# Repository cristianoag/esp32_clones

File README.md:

# The Retro Hacker Clone Series

The Retro Hacker Clone Series brings together hardware designs and source-available firmware to recreate and emulate classic computers from the 1980s and 1990s using modern ESP32 based hardware.

 The board is designed to feel like a small retro computer rather than a bare dev board, and the firmwares are built to be practical, tweakable, and easy to build from a standard Git checkout.

## Hardware versions

The series now has two hardware versions that share the same outline, mounting holes and connector layout:

| Version | Module | Audio | KiCad project |
| --- | --- | --- | --- |
| ESP32-S3 | ESP32-S3 dev board (N16R8) | Mono | [hardware/esp32_s3_clones](hardware/esp32_s3_clones) |
| ESP32-P4 | Waveshare ESP32-P4-Core-DEV-KIT | Stereo | [hardware/esp32_p4_clones](hardware/esp32_p4_clones/README.md) |

## Software

At the moment the series includes eight emulator builds, all for the ESP32-S3 board. There is no firmware for the ESP32-P4 board yet.

| Firmware | Covered machines | ESP32-S3 | ESP32-P4 |
| --- | --- | --- | --- |
| CP400 | Prologica CP400 / CoCo 2 | [Setup guide](software/esp32_s3_cp400/README.md) and [change log](software/esp32_s3_cp400/docs/log.md) | Not available yet |
| MSX | MSX1, MSX2, and MSX2+ | [Setup guide](software/esp32_s3_msx/README.md) and [change log](software/esp32_s3_msx/docs/log.md) | Not available yet |
| MSX TurboR (experimental) | Panasonic FS-A1ST | [Setup guide](software/esp32_s3_msxturbor/README.md), [license report](software/esp32_s3_msxturbor/docs/licenses.md) and [change log](software/esp32_s3_msxturbor/docs/log.md) | Not available yet |
| TK90X / TK95 | Microdigital TK90X (48 KiB) and TK95 | [Setup guide](software/esp32_s3_tk95/README.md) and [change log](software/esp32_s3_tk95/docs/log.md) | Not available yet |
| Apple II | Generic Apple II+ and original Apple IIe | [Setup guide](software/esp32_s3_apple2/README.md) and [change log](software/esp32_s3_apple2/docs/log.md) | Not available yet |
| Macintosh Plus | Apple Macintosh Plus | [Setup guide](software/esp32_s3_macplus/README.md) and [change log](software/esp32_s3_macplus/docs/log.md) | Not available yet |
| Sega Master System | Sega Master System (NTSC / PAL) | [Setup guide](software/esp32_s3_sms/README.md) and [change log](software/esp32_s3_sms/docs/log.md) | Not available yet |
| Commodore 64 | Commodore 64 (PAL) | [Setup guide](software/esp32_s3_c64/README.md), [licenses](software/esp32_s3_c64/docs/licenses.md) and [change log](software/esp32_s3_c64/docs/log.md) | Not available yet |

> **Development status:** all firmwares are under active development and at different maturity stages. The CP400 and MSX firmwares are the most mature; the others (including the experimental MSX TurboR) are earlier-stage and may be incomplete or change significantly.

All eight builds share the same ESP32-S3 board, VGA output, USB keyboard input, SD-card storage, and a simple F12 menu for setup and firmware updates.

## User guides

- [Quick Start](docs/quick-start.md): connect the monitor, keyboard and
  joysticks, turn on/reset the computer, and switch firmware through F12.
- [User Manual](docs/user-manual.md): SD-card preparation, controller
  compatibility, game-loading steps for all eight firmwares, and troubleshooting.

### Switching emulators

With the current updater and shared dual 4 MiB OTA layout installed, open
**F12 > Firmware update** in any emulator and select another emulator's
`.FLH` package. For example, MSX can install CP400, and CP400 can then
install Apple II. No renaming is needed. Copy the packages to the FAT32
card root (required by CP400's file picker), prepare the destination
emulator's ROMs using its setup guide, confirm the update and keep power
connected until the board restarts. The original FLH stays on the card.

Build packages with `make firmware` in each firmware folder. Older MSX,
TK and Apple updaters reject other emulator filenames: first update to
the current build of the **same** emulator. Older CP400 installations use
a smaller partition layout and require a **one-time UART upload** of a
current build before switching via SD. FLH updates replace only the
application, not the bootloader or partition table. Use current builds
for every destination so switching remains available after reboot.
Checksums detect corruption, not authenticity; install only trusted
firmware built for this board.

After building all eight packages, run
`powershell -ExecutionPolicy Bypass -File .\software\Test-FirmwareCompatibility.ps1`
to check the shared layout and all 64 source/destination combinations
against mock OTA storage. Physical-board switching still needs validation.

## Commodore 64

The [C64 firmware](software/esp32_s3_c64/README.md) adapts the
CPU, CIA, VIC-II and SID from
[retroelec/T-HMI-C64](https://github.com/retroelec/T-HMI-C64) to the shared
VGA board. It includes a USB C64 keyboard matrix, two calibrated USB
joysticks with port swapping, PWM sound, PRG loading, read-only D64 program
extraction, the F12 configuration menu and interchangeable FLH firmware.
Supply your own BASIC, KERNAL and character ROMs. The initial version
does not emulate a 1541 drive, cartridges or tapes, and does not claim
cycle accuracy or verified physical-board performance.

## CP400

The Prologica CP400 was one of the more recognizable Brazilian home computers of the 1980s. It was compatible with the Tandy/Radio Shack TRS-80 Color Computer 2, but it had its own industrial design, Brazilian-language software ecosystem, and local hardware expectations.

The [CP400 firmware](software/esp32_s3_cp400/README.md) recreates that environment on ESP32-S3 hardware, including MC6809 emulation, VGA output, native USB keyboard support, joystick inputs, SD storage, virtual floppy handling, and the F12 configuration/update menu.

## MSX

The MSX has a very special place in Brazilian computing history. It officially arrived in Brazil in 1985 through two locally produced machines: the HotBit, from Sharp/Epcom, and the Expert, from Gradiente. At a time when Brazil’s computer market was heavily restricted and imported machines were difficult and expensive to obtain, the MSX became one of the country’s most important home-computing platforms. Its standardized architecture, large software library, expandability, and built-in BASIC introduced an entire generation not only to games, but also to programming, electronics, and computer technology. 

The [MSX firmware](software/esp32_s3_msx/README.md) runs the original fMSX core on the same shared board. It includes multiple BIOS profiles for Omega MSX2+, Gradiente Expert 1.1, Sharp Hotbit 1.2, and Panasonic FS-A1WSX / FS-A1F / FS-A1FX.

The software supports the core MSX experience with USB keyboard input, graphics, sound, cartridge booting, and firmware updates through the on-screen menu. and... USB joystick support, of course.

The F12 Media menu attaches writable `.dsk` images to drives A/B and read-only `.cas` tapes, with ejection, tape rewind and optional saved boot defaults. Disk access requires a compatible user-supplied disk BIOS; see the [disk and tape setup guide](software/esp32_s3_msx/README.md#disk-and-tape-images).

## MSX TurboR / Panasonic FS-A1ST

The experimental [MSX TurboR firmware](software/esp32_s3_msxturbor/README.md)
recreates the Panasonic FS-A1ST using a source subset of blueMSX, separate
from the ordinary fMSX-based MSX build. It includes Z80/R800 switching,
DRAM mode, V9958 graphics, PSG, MSX-MUSIC, PCM output and writable
360/720 KiB `.dsk` images through the original disk interface.

Supply your own FS-A1ST firmware and Kanji ROMs under
`msxturbor/bios/fs-a1st` on the FAT32 card. See the
[SD card and ROM setup](software/esp32_s3_msxturbor/README.md#prepare-the-sd-card),
[scope and limitations](software/esp32_s3_msxturbor/README.md#implementation-scope-and-limitations)
and [licenses and provenance](software/esp32_s3_msxturbor/docs/licenses.md).
The original BIOS boots into MSX BASIC in host tests; physical-board
performance, VGA/audio quality and firmware switching still require
validation. A1GT/MIDI and full-speed emulation are not claimed.

## TK90X / TK95

The Microdigital TK90X and TK95 brought the ZX Spectrum family of computers to Brazilian homes. The [TK firmware](software/esp32_s3_tk95/README.md) emulates the TK95 and 48 KiB TK90X on the same shared ESP32-S3 board, using
the cycle-stepped chips Z80 core.

The firmware includes VGA output, USB keyboard input, beeper audio and two USB joystick ports with calibration and selectable Kempston, Sinclair 1/2 or Cursor interfaces. The F12 menu brings together machine and ROM selection, 50/60 Hz Microdigital ULA timing, Portuguese/Spanish ROM language selection, sound and volume, saved boot defaults, reset options and firmware updates.

Media support includes read-only standard `.tap` playback and loading 48K `.sna` and `.z80` snapshots. Supply legally obtained, raw 16 KiB ROMs at `tk\bios\tk95.rom` and `tk\bios\tk90.rom` on the FAT32 card; the `tk` folder can sit alongside `msx` and `cp400`. No ROM bytes are embedded in the firmware.

See the [SD card and ROM setup](software/esp32_s3_tk95/README.md#sd-card-and-roms) and [keyboard guide](software/esp32_s3_tk95/README.md#keyboard-and-joysticks) for the original TK keyword-entry conventions.

The initial release does not include AY audio, Betadisk, TZX, tape recording or snapshot saving, and does not claim full cycle accuracy. 

## Apple II

The [Apple II firmware](software/esp32_s3_apple2/README.md) adds generic
Apple II+ (64 KiB with language card) and original Apple IIe (128 KiB)
profiles. It follows the shared standalone PlatformIO, board-driver, F12
configuration and FLH firmware-update conventions.

The initial integration uses
[codesafe/ESP32-VGA_AppleII_Emulator](https://github.com/codesafe/ESP32-VGA_AppleII_Emulator)
as its starting reference, with a cycle-stepped NMOS 6502 and additional
IIe banking and display support. VGA preserves the full width of
80-column text; USB keyboard, calibrated joystick/paddle input, speaker
audio and two read-only NIB Disk II drives are included.

Supply machine and Disk II ROMs under `apple2/bios` on SD. No ROMs or games
are distributed. Enhanced IIe/65C02 and Brazilian TK2000, TK3000/Compact,
MC-4000/Exato and Exato IIe profiles are not claimed as supported without
their required hardware and verified ROMs. See the
[scope and limitations](software/esp32_s3_apple2/README.md#supported-media-and-limitations).
Physical-board validation is still pending.

## Macintosh Plus

The [Macintosh Plus firmware](software/esp32_s3_macplus/README.md)
integrates a Musashi 68000 and Macintosh peripheral core with 4 MiB of
emulated RAM, a native 512x342 monochrome image centered on 640x480 VGA,
USB keyboard input, mono audio and the shared F12 menu and FLH updater.
A direct low-speed HID boot mouse connects to **joystick port 2**;
full-speed-only mice and USB hubs are unsupported.

Supply an unmodified 128 KiB Macintosh Plus ROM and a bootable whole
SCSI disk image under `macplus/bios` and `macplus/disks` on the FAT32 card.
No Apple ROM, operating system or disk image is bundled. See the
[SD card, ROM and disk setup](software/esp32_s3_macplus/README.md#sd-card-and-rom),
[mouse compatibility](software/esp32_s3_macplus/README.md#mouse-compatibility)
and [scope and validation](software/esp32_s3_macplus/README.md#scope-and-validation).
This is an initial integration, not a claim of full-speed or cycle-accurate
emulation; floppy-media support is not implemented.

## Repository layout

```text
hardware/esp32_s3_clones/          KiCad PCB and shared board files
hardware/esp32_s3_clones/libraries Local KiCad symbols and footprints
hardware/esp32_s3_clones/bom       Interactive BOM and BOM assets
hardware/esp32_p4_clones/          KiCad PCB for the ESP32-P4 (stereo audio) variant, see its README
hardware/cases/standard/       Parametric printed base, acrylic lid and manufacturing exports
software/esp32_s3_cp400/  PlatformIO firmware for the CP400 build
software/esp32_s3_msx/    MSX firmware and setup files
software/esp32_s3_msxturbor/ MSX TurboR / Panasonic FS-A1ST firmware and setup files
software/esp32_s3_tk95/   TK90X/TK95 firmware and setup files
software/esp32_s3_apple2/ Apple II+/original IIe firmware and setup files
software/esp32_s3_macplus/ Macintosh Plus firmware and setup files
images/                         Generated images and project documentation assets
```

## Board renderings

For the first enclosure prototype, see the
[standard case manufacturing files and engineering report](hardware/cases/standard/README.md).
P4 combines a printed base with easy-loading PCB nut traps, a screw-fastened
upper and a drilled 3 mm acrylic lid. Four M3 x 25 nylon screws pass down through
the acrylic into base nuts. Its vented alternative uses a separate matching
base with recessed bottom-entry screws and upper nuts. The acrylic cutting
pattern is [lid.dxf](hardware/cases/standard/lid.dxf); do not reuse the old
plain panel. See the report for dimensions and remaining physical-fit checks.

The Hotbit-inspired **Compact Classic C6** fits the same PCB in a
**124 x 74 x 39.1 mm** case, reducing the earlier Classic footprint by 26.9%.
It retains the miniature keyboard, photo-inspired colours and closed decorative
grille, with underside M3 cover screws. Use the matching
[base STL](hardware/cases/hb-8000/classic_base.stl) and
[upper STL](hardware/cases/hb-8000/classic_upper.stl); do not mix these with older
Classic or Wasteland halves. See the
[assembled/exploded preview](hardware/cases/hb-8000/classic_preview.png).
Print both STLs at 100%; the upper needs removable interior supports.
PCB screws remain M3 x 8 with 1 mm nylon washers; cover screws are M3 x 25 nylon,
with four M3 hex nuts for each set. Physical plug-fit and thermal tests are
still required; the decorative grille is not a ventilation opening.

The [Sony S2](hardware/cases/sony/README.md),
[Panasonic P2](hardware/cases/panasonic/README.md) and
[Apple II A3](hardware/cases/apple2/README.md) now share the C6 base and its
bottom-entry shell fastening. Their matching uppers replace the old clip joints.

The [Mac Plus-inspired M1](hardware/cases/mac/README.md) uses the same C6 base
under a **124 x 74 x 146.1 mm upright tower**, with a separate dark decorative
screen and miniature keyboard. Its blind floppy-slot detail, top grilles and
handle-shaped recess follow the supplied visual reference; no working display,
keyboard electronics or load-bearing handle is included. See the
[assembly and print-layout preview](hardware/cases/mac/mac_preview.png).

The [CP400-inspired CP1](hardware/cases/cp400/README.md) also reuses the C6
base in the compact **124 x 74 x 39.1 mm** envelope. Its left keyboard, raised
right panel and horizontal rear grilles follow the supplied photograph.
Integral and separate-keyboard upper options are available; red/green/cyan
accents in the [preview](hardware/cases/cp400/cp400_preview.png) are a painting
guide, not separate key pieces.

The [Master System-inspired SMS1](hardware/cases/sms/README.md) uses the same
C6 base and **124 x 74 x 39.1 mm** envelope, with an angular black console
shell and one separately printed red top-panel/front-stripe insert.
Cartridge/card slots and control shapes are decorative; no joystick or
controller is modelled. See the
[assembly and print-layout preview](hardware/cases/sms/sms_preview.png).

The PCB below is the current KiCad board layout for the shared ESP32 clone board. The front and back views are generated directly from the project PCB.

<div align="center">

</div>

For the full component-by-component assembly view, open the [interactive BOM](https://htmlpreview.github.io/?https://raw.githubusercontent.com/cristianoag/esp32_clones/blob/main/hardware/esp32_s3_clones/bom/ibom.html).

## Hardware summary

The ESP32-S3 board is built around an ESP32-S3 DevKitC-style N16R8 module with 16 MB flash and 8 MB OPI PSRAM. It includes VGA output, a USB keyboard port, SD/MMC storage, a mono audio output, and a compact layout intended to behave more like a small computer than a bare dev board.

The ESP32-P4 board keeps the same outline, VGA output, USB-A ports, SD card slot and connector positions, but uses the Waveshare ESP32-P4-Core-DEV-KIT (32 MB flash, 32 MB PSRAM) and adds a stereo audio output.

The ESP32-S3 board is used by all eight firmware projects, and the pin mapping is documented in the [MSX hardware section](software/esp32_s3_msx/README.md#hardware), the [MSX TurboR hardware section](software/esp32_s3_msxturbor/README.md#hardware-and-dependencies), the [TK hardware section](software/esp32_s3_tk95/README.md#hardware), the [Apple II hardware section](software/esp32_s3_apple2/README.md#hardware) and the [Macintosh Plus hardware section](software/esp32_s3_macplus/README.md#hardware).

## BOM and purchasing

This is the current BOM for the board as defined in the KiCad project. The table is meant to be a quick parts reference for ordering and build prep.

| Component | Description | Qty | Package | AliExpress |
| --- | --- | ---: | --- | --- |
| C1 | 220 µF electrolytic capacitor | 1 | 6.3x3 mm | [AliExpress](https://s.click.aliexpress.com/e/_c3vZZzuN) |
| C2 | 10 µF electrolytic capacitor | 1 | 5x4.5 mm | [AliExpress](https://s.click.aliexpress.com/e/_c3vZZzuN) |
| C4 | 100 nF ceramic capacitor | 1 | 0805 | [AliExpress](https://s.click.aliexpress.com/e/_c31gzw17) |
| C6 | 47 nF ceramic capacitor | 1 | 0805 | [AliExpress](https://s.click.aliexpress.com/e/_c31gzw17) |
| F1 | Resettable fuse / polyfuse | 1 | 1210 | [AliExpress](https://s.click.aliexpress.com/e/_c36cHi81) |
| J1 | DC barrel jack | 1 | Horizontal | [AliExpress](https://s.click.aliexpress.com/e/_c3D102dx) |
| J2 | Micro SD card socket | 1 | uSD | [AliExpress](https://s.click.aliexpress.com/e/_c3odXI41) |
| J3 | 3.5 mm audio jack | 1 | PJ-307 | [AliExpress](https://s.click.aliexpress.com/e/_c4DX94lF) |
| J4 | 12V power header / connector | 1 | PS-12E05 | [AliExpress](https://s.click.aliexpress.com/e/_c42cnGRn) |
| J5 | 5V power header / connector | 1 | PS-22F05 | [AliExpress](https://s.click.aliexpress.com/e/_c35YnsCh) |
| J6–J8 | USB-A connector | 3 | TE 6364372-2 | [AliExpress](https://s.click.aliexpress.com/e/_c4afTAHb) |
| J9 | DB15 video connector | 1 | D-sub 15-pin | [AliExpress](https://s.click.aliexpress.com/e/_c3K7eRWv) |
| R1, R4, R7 | 10 kΩ resistor | 3 | 0805 | [AliExpress](https://s.click.aliexpress.com/e/_c2zrvGiH) |
| R8, R10, R12 | 1.2 kΩ resistor | 3 | 0805 | [AliExpress](https://s.click.aliexpress.com/e/_c2zrvGiH) |
| R9, R11, R13 | 560 Ω resistor | 3 | 0805 | [AliExpress](https://s.click.aliexpress.com/e/_c2zrvGiH) |
| R2, R5 | 330 Ω resistor | 2 | 0805 | [AliExpress](https://s.click.aliexpress.com/e/_c2zrvGiH) |
| U1 | ESP32-S3-WROOM-1 module | 1 | ESP32-S3-WROOM-1 | [AliExpress](https://s.click.aliexpress.com/e/_c2uppnEv) |

## Firmware build notes

Firmware project folders use `software/esp32_s3_<name>`, while update packages
retain their existing `ESP32_<NAME>-X.YY.FLH` names.

All six firmware projects use PlatformIO with the Arduino framework and a pinned `espressif32@6.11.0` platform. From the project directory you want to use, run:

```powershell
Set-Location .\software\esp32_s3_cp400
# or:
# Set-Location .\software\esp32_s3_msx
# or:
# Set-Location .\software\esp32_s3_msxturbor
# or:
# Set-Location .\software\esp32_s3_tk95
# or:
# Set-Location .\software\esp32_s3_apple2
# or:
# Set-Location .\software\esp32_s3_macplus

make firmware
```

The build produces FLH packages for each target; the project directories keep their own firmware images and configuration.
From `software`, run `make` to prepare the shared SD-card tree and copy each
emulator's highest-versioned `dist\ESP32_*-X.YY.FLH` package only to the root of
`software\sdcard`. Firmware packages are copied
after merging the SD-card trees, including with parallel `make`.
Run `make firmware` there to copy packages only, or `make sdcard`
to prepare the SD-card tree only. Packages are not rebuilt; if any emulator is
missing a package, copying fails before any firmware files are deleted or copied.
Before copying, all FLH files directly in the shared SD-card root are deleted,
leaving only the latest package for each emulator. Emulator project roots and
`dist` archives are left unchanged, as are non-FLH files and nested folders
during firmware copying.
Each firmware directory includes its own board definitions and required
library sources and can be copied and compiled independently of the others.
All six still require PlatformIO and the configured ESP32 toolchain.

## ROMs and original software

Original CP400, CoCo, MSX, MSX TurboR, TK90X/TK95, ZX Spectrum, Apple II, Macintosh Plus, BASIC, cartridge, cassette, floppy and hard-disk software may still be copyrighted. This repository is for original hardware, firmware, and project files. Use legally obtained ROMs and software images when needed.

The CP400 firmware loads its BIOS files from `software/esp32_s3_cp400/sdcard/cp400/bios`. Copy the `cp400` folder to the root of the microSD card so the firmware can read the BASIC, Extended BASIC, and CP400 or CoCo disk controller ROM selected in the F12 menu.

## Historical notes

The CP400 was part of the wider Brazilian TRS-Color ecosystem, the MSX line became one of the most important home computer families in Brazil, and Microdigital's TK90X and TK95 connected Brazilian users to the ZX Spectrum ecosystem. This project sits at the intersection of those histories: a practical board, six emulator builds, and a small bit of preservation work for machines that still matter to a lot of people.

## References

- [Prologica CP-400](https://en.wikipedia.org/wiki/Prol%C3%B3gica_CP-400)
- [CP400](https://pt.wikipedia.org/wiki/CP400)
- [TRS-80 Color Computer](https://en.wikipedia.org/wiki/TRS-80_Color_Computer)
- [MSX](https://en.wikipedia.org/wiki/MSX)
- [fMSX by Marat Fayzullin](https://fms.komkon.org/fMSX/)
- [TK90X](https://en.wikipedia.org/wiki/TK90X)
- [TK95](https://en.wikipedia.org/wiki/TK95)
- [ESPectrum reference emulator](https://github.com/EremusOne/ESPectrum)
- [chips Z80 core](https://github.com/floooh/chips)
- [Prologica](https://pt.wikipedia.org/wiki/Prol%C3%B3gica)
- [Datassette](https://datassette.org/)

## License

All hardware and firmware binaries in this repository are released under the Creative Commons Attribution-NonCommercial-ShareAlike 4.0 International license. Personal builds and community tinkering are encouraged, but commercial use or resale requires explicit authorization from the author.

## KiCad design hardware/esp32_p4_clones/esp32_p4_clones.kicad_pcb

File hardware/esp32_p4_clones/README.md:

# ESP32-P4 Clone Board

KiCad 10 project for the ESP32-P4 version of the shared clone board. It reuses the
outline, mounting holes and connector positions of
[`../esp32_s3_clones`](../esp32_s3_clones) (110 x 60 mm), but carries a Waveshare
[ESP32-P4-Core-DEV-KIT](https://docs.waveshare.com/ESP32-P4-Core-DEV-KIT) instead of the
ESP32-S3 dev board, and has **stereo** audio.

Open `esp32_p4_clones.kicad_pro`. The libraries are local to the project
(`libraries/`), so no global library setup is needed.

## What changed from the S3 board

| Area | S3 board | P4 board |
| --- | --- | --- |
| Module | ESP32-S3 dev board, 2 x 22 pins | ESP32-P4-Core-DEV-KIT, 2 x 20 pins (28.62 x 58 mm), USB-C end towards the board edge |
| Audio | Mono, one filtered output feeding tip and ring | Stereo: two identical RC chains (330 Ω / 47 nF, 330 Ω / 100 nF, 10 µF coupling) feeding tip (left) and ring (right) |
| USB-A J7 | GPIO software host | Native USB 2.0 high-speed host (`DM`/`DP`) |
| Power into the module | `5V` pin | `VSYS` pin (the dev kit's own USB-C ports can also power the board) |
| Reset button J5 | `RST` | `RUN` (chip enable) |
| SD card | `DAT3` unconnected | `DAT3` pulled up with R4 (CLK has no pull-up) |

New or renumbered parts: C3 (10 µF), C5 (100 nF), C7 (47 nF), R3 and R6 (330 Ω) for the
right audio channel. Everything else keeps its S3 reference designator and footprint.

## GPIO map

| Function | Dev kit pin | Net |
| --- | --- | --- |
| VGA red (1.2 kΩ / 560 Ω) | GPIO4 / GPIO5 | `VGA_R0` / `VGA_R1` |
| VGA green (1.2 kΩ / 560 Ω) | GPIO9 / GPIO10 | `VGA_G0` / `VGA_G1` |
| VGA blue (1.2 kΩ / 560 Ω) | GPIO11 / GPIO13 | `VGA_B0` / `VGA_B1` |
| VGA HSYNC / VSYNC | GPIO3 / GPIO2 | `VGA_HS` / `VGA_VS` |
| Audio left / right | GPIO48 / GPIO47 | `AUDIO_L` / `AUDIO_R` |
| SD card CLK / CMD / DAT0 | GPIO46 / GPIO33 / GPIO32 | `SD_CLK` / `SD_CMD` / `SD_D0` |
| USB-A J7 (native) D- / D+ | DM / DP | `USB_DM` / `USB_DP` |
| USB-A J6 D- / D+ | GPIO26 / GPIO27 | `J6_DM` / `J6_DP` |
| USB-A J8 D- / D+ | GPIO20 / GPIO21 | `J8_DM` / `J8_DP` |
| Reset button | RUN | `RESET` |

GPIO2 to GPIO13 and GPIO20 to GPIO48 used above are all on the dev kit's 2.54 mm headers.
GPIO6, GPIO12, GPIO22, GPIO23, GPIO53 and GPIO54 are left unconnected. GPIO7 and GPIO8 are
the dev kit's I2C pins with 2.2 kΩ pull-ups, so they are also left free. `VBUS` and `EN`
are not connected.

## Check before ordering boards

- **Header row spacing is assumed to be 25.4 mm.** Waveshare publishes the board size
  (28.62 x 58 mm), the 2.54 mm pitch and the first pin 4.87 mm from each end, but not the
  distance between the two rows. Measure your dev kit and adjust the footprint
  (`libraries/footprints/ESP32.pretty/ESP32-P4-Core-DEV-KIT.kicad_mod`) if it differs.
- The dev kit's USB-C overhang and the 3D model (`libraries/ESP32-P4-Core-DEV-KIT.py`
  generates the STEP) are approximations.
- The PJ-307 jack pads are named `G`, `S` and `T`. They are wired as sleeve = `G`,
  tip (left) = `T`, ring (right) = `S`. If the channels come out swapped on your jack, swap
  `JACK_L` and `JACK_R`.
- The board was auto-routed with Freerouting and passes ERC and DRC. Review the routing,
  especially the J7 USB D+/D- pair, which is not length matched or impedance controlled.
- Do not feed 5 V into both the barrel jack and the dev kit's USB-C ports at the same time
  unless you are sure the supplies are compatible.

The remaining DRC warnings are silkscreen clearances on the connector footprints inherited
from the S3 board.

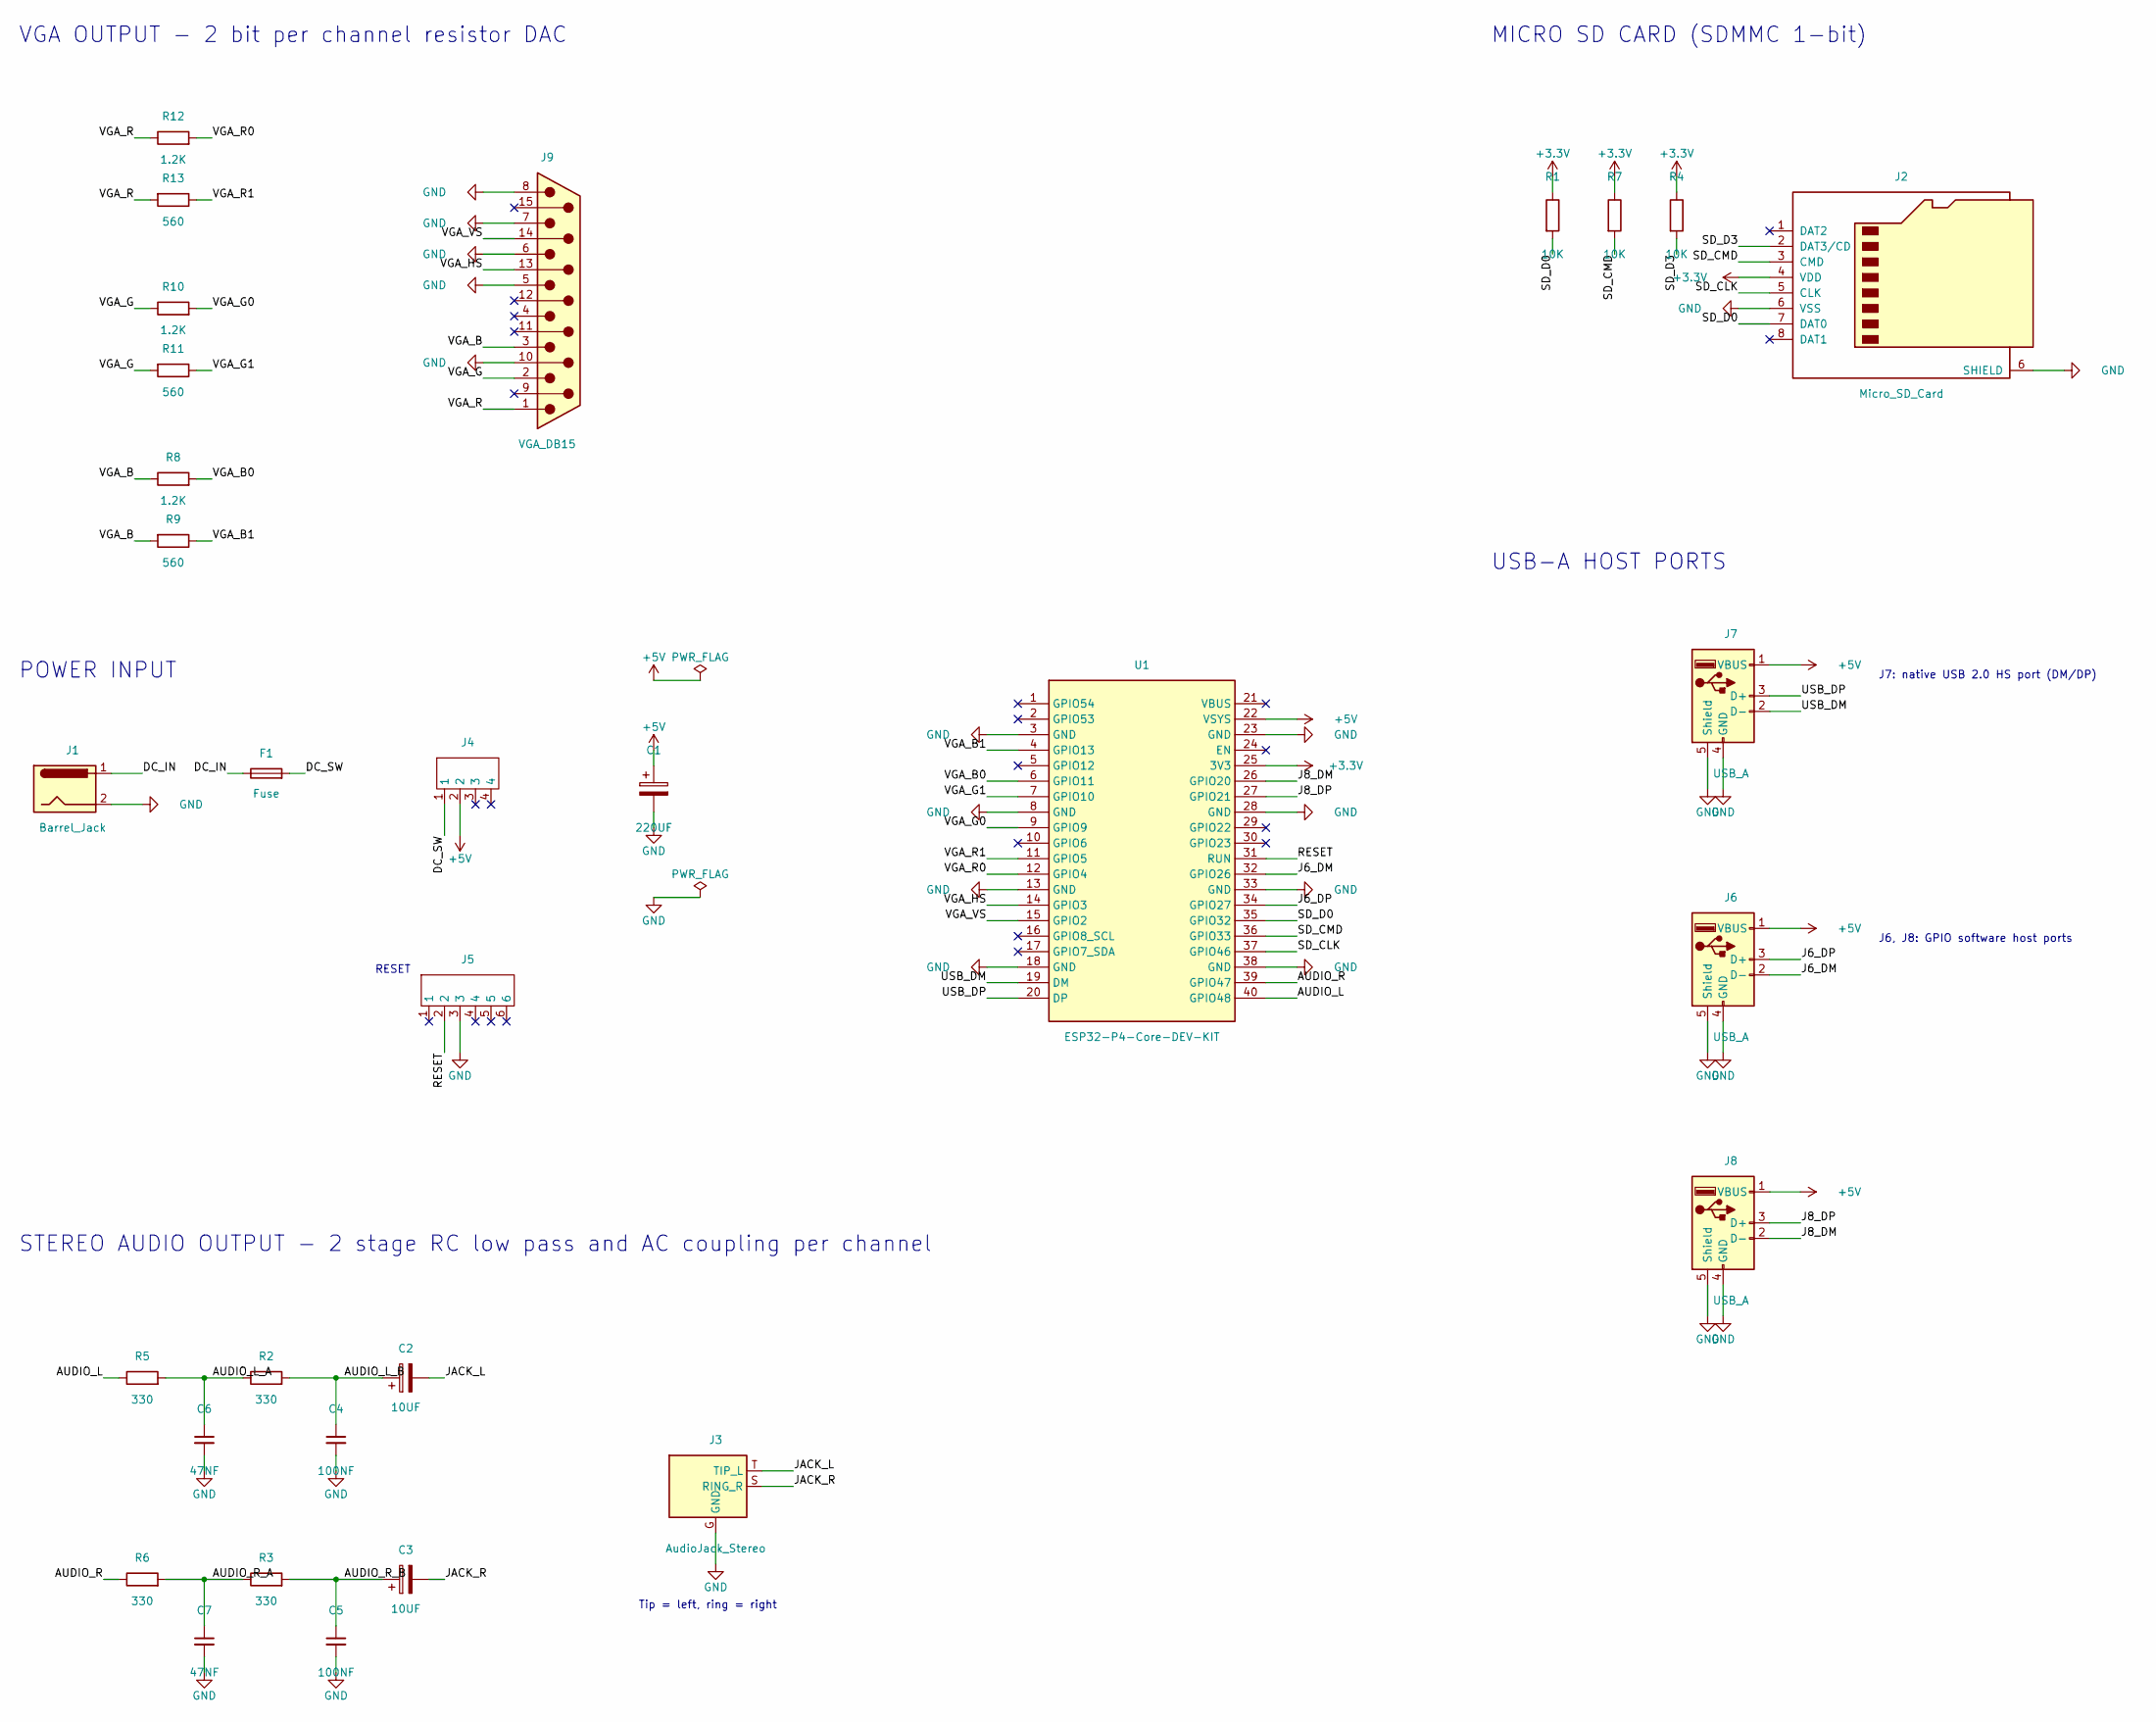
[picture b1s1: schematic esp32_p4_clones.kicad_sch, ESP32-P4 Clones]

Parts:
C1: 220UF; CP_Elec_6.3x3
C2, C3: 10UF; CP_Elec_5x4.5
C4, C5: 100NF; C_0805_2012Metric_Pad1.18x1.45mm_HandSolder
C6, C7: 47NF; C_0805_2012Metric_Pad1.18x1.45mm_HandSolder
F1: Fuse; Fuse_1210_3225Metric
J1: Barrel_Jack; BarrelJack_Horizontal
J2: Micro_SD_Card; Conn_uSDcard
J3: AudioJack_Stereo; PJ-307
J4: PS-12E05
J5: PS-22F05
J6, J7, J8: USB_A; TE_6364372-2
J9: VGA_DB15; DSUB-15-HD_Socket_Horizontal_P2.29x1.90mm_EdgePinOffset3.03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
R1, R4, R7: 10K; R_0805_2012Metric_Pad1.20x1.40mm_HandSolder
R2, R3, R5, R6: 330; R_0805_2012Metric_Pad1.20x1.40mm_HandSolder
R8, R10, R12: 1.2K; R_0805_2012Metric_Pad1.20x1.40mm_HandSolder
R9, R11, R13: 560; R_0805_2012Metric_Pad1.20x1.40mm_HandSolder
U1: ESP32-P4-Core-DEV-KIT

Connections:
+3.3V: J2.4 (VDD), R1.1, R4.1, R7.1, U1.25 (3V3)
+5V: C1.1, J4.2, J6.1 (VBUS), J7.1 (VBUS), J8.1 (VBUS), U1.22 (VSYS)
/AUDIO_L: R5.1, U1.40 (GPIO48)
/AUDIO_L_A: C6.1, R2.1, R5.2
/AUDIO_L_B: C2.1, C4.1, R2.2
/AUDIO_R: R6.1, U1.39 (GPIO47)
/AUDIO_R_A: C7.1, R3.1, R6.2
/AUDIO_R_B: C3.1, C5.1, R3.2
/DC_IN: F1.1, J1.1
/DC_SW: F1.2, J4.1
/J6_DM: J6.2 (D-), U1.32 (GPIO26)
/J6_DP: J6.3 (D+), U1.34 (GPIO27)
/J8_DM: J8.2 (D-), U1.26 (GPIO20)
/J8_DP: J8.3 (D+), U1.27 (GPIO21)
/JACK_L: C2.2, J3.T (TIP_L)
/JACK_R: C3.2, J3.S (RING_R)
/RESET: J5.2, U1.31 (RUN)
/SD_CLK: J2.5 (CLK), U1.37 (GPIO46)
/SD_CMD: J2.3 (CMD), R7.2, U1.36 (GPIO33)
/SD_D0: J2.7 (DAT0), R1.2, U1.35 (GPIO32)
/SD_D3: J2.2 (DAT3/CD), R4.2
/USB_DM: J7.2 (D-), U1.19 (DM)
/USB_DP: J7.3 (D+), U1.20 (DP)
/VGA_B: J9.3, R8.1, R9.2
/VGA_B0: R8.2, U1.6 (GPIO11)
/VGA_B1: R9.1, U1.4 (GPIO13)
/VGA_G: J9.2, R10.1, R11.2
/VGA_G0: R10.2, U1.9 (GPIO9)
/VGA_G1: R11.1, U1.7 (GPIO10)
/VGA_HS: J9.13, U1.14 (GPIO3)
/VGA_R: J9.1, R12.1, R13.2
/VGA_R0: R12.2, U1.12 (GPIO4)
/VGA_R1: R13.1, U1.11 (GPIO5)
/VGA_VS: J9.14, U1.15 (GPIO2)
GND: C1.2, C4.2, C5.2, C6.2, C7.2, J1.2, J2.6 (VSS), J3.G (GND), J5.3, J6.4 (GND), J6.5 (Shield), J7.4 (GND), J7.5 (Shield), J8.4 (GND), J8.5 (Shield), J9.5, J9.6, J9.7, J9.8, J9.10, U1.3 (GND), U1.8 (GND), U1.13 (GND), U1.18 (GND), U1.23 (GND), U1.28 (GND), U1.33 (GND), U1.38 (GND)

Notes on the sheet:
VGA OUTPUT - 2 bit per channel resistor DAC
POWER INPUT
RESET
MICRO SD CARD (SDMMC 1-bit)
USB-A HOST PORTS
J7: native USB 2.0 HS port (DM/DP)
J6, J8: GPIO software host ports
STEREO AUDIO OUTPUT - 2 stage RC low pass and AC coupling per channel
Tip = left, ring = right

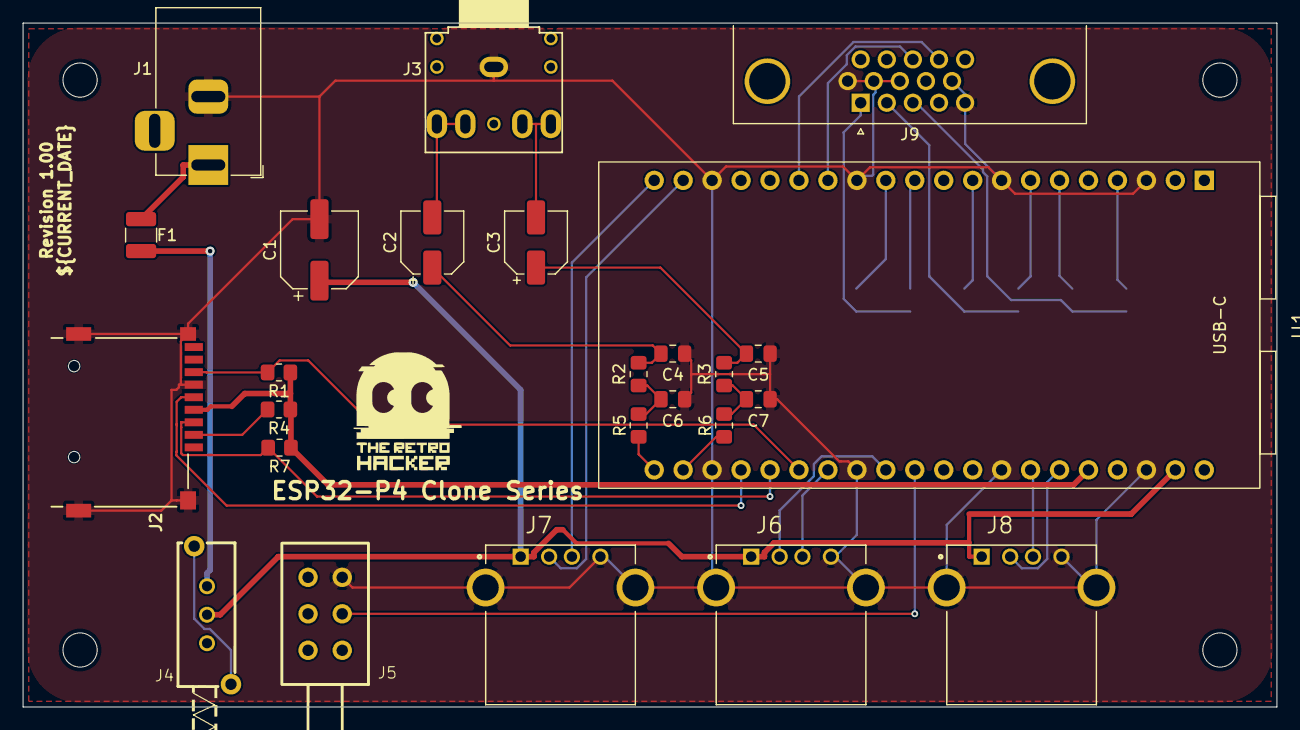
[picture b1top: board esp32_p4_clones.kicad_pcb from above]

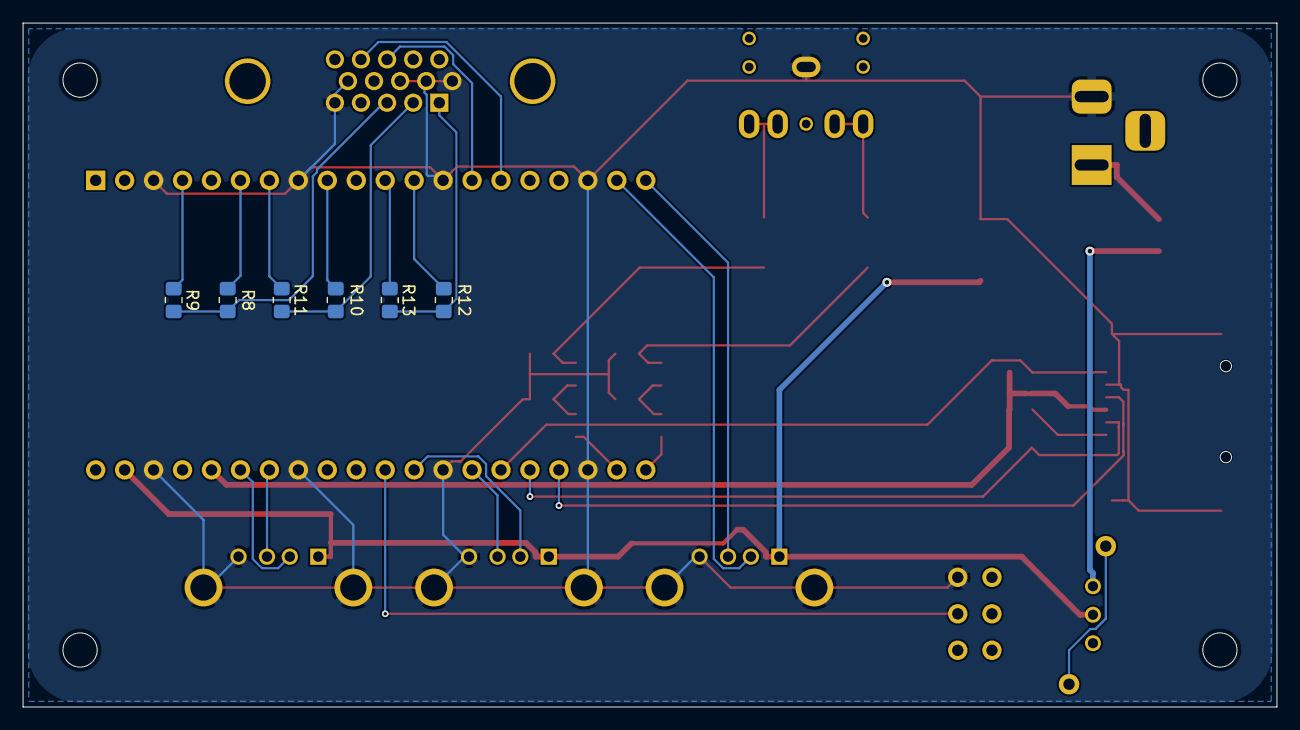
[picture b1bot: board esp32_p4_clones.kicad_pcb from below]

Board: 2 copper layers, 110.0 x 60.0 mm, 31 parts (6 on the bottom side), 35 nets.

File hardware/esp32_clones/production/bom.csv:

Designator,Footprint,Quantity,Value,LCSC Part #
C1,CP_Elec_6.3x3,1,220UF,
C2,CP_Elec_5x4.5,1,10UF,
C4,0805,1,100NF,
C6,0805,1,47NF,
F1,1210,1,Fuse,
J1,BarrelJack_Horizontal,1,Barrel_Jack,
J2,Conn_uSDcard,1,Micro_SD_Card,
J3,PJ-307,1,AudioJack2_Ground,
J4,PS-12E05,1,~,
J5,PS-22F05,1,~,
"J6, J7, J8",TE_6364372-2,3,USB_A,
J9,DSUB-15-HD_Socket_Horizontal_P2.29x1.90mm_EdgePinOffset3.03mm_Housed_MountingHolesOffset4.94mm,1,DA15_Pins,
"R1, R4, R7",0805,3,10K,
"R10, R12, R8",0805,3,1.2K,
"R11, R13, R9",0805,3,560,
"R2, R5",0805,2,330,
U1,ESP32-S3-WROOM-1,1,~,

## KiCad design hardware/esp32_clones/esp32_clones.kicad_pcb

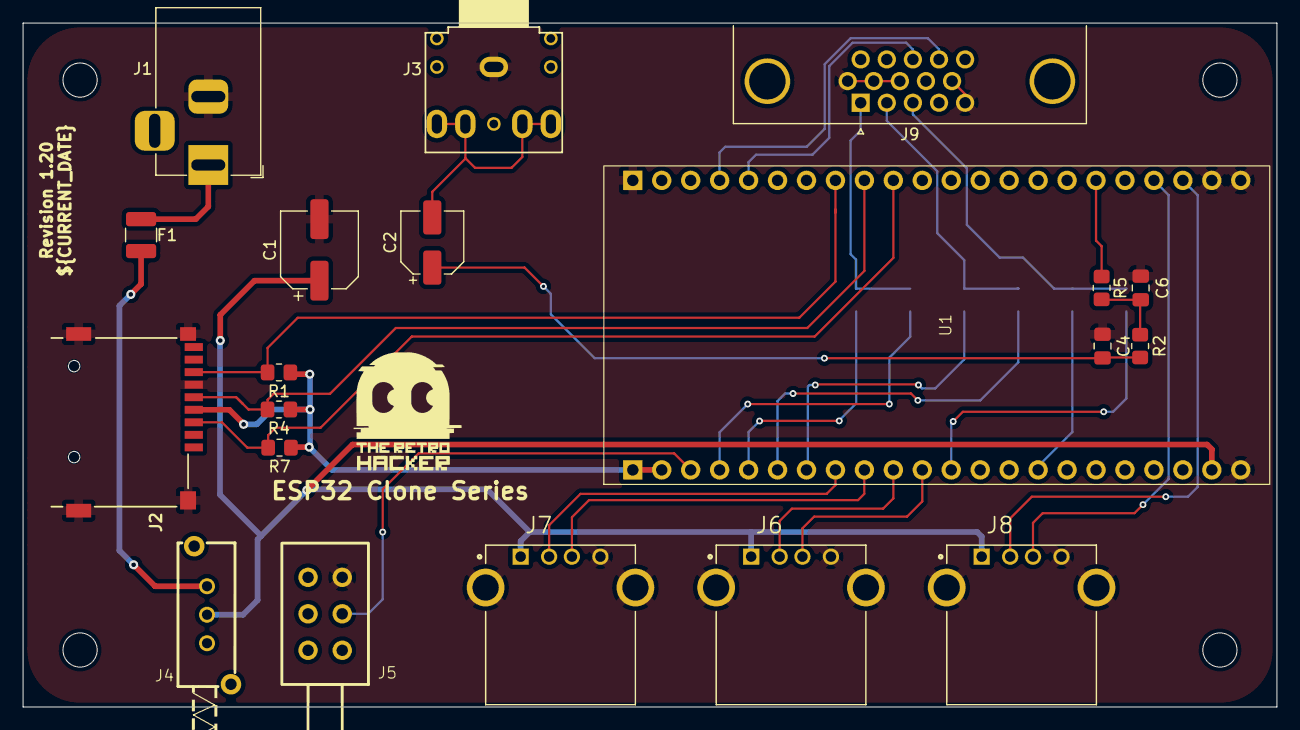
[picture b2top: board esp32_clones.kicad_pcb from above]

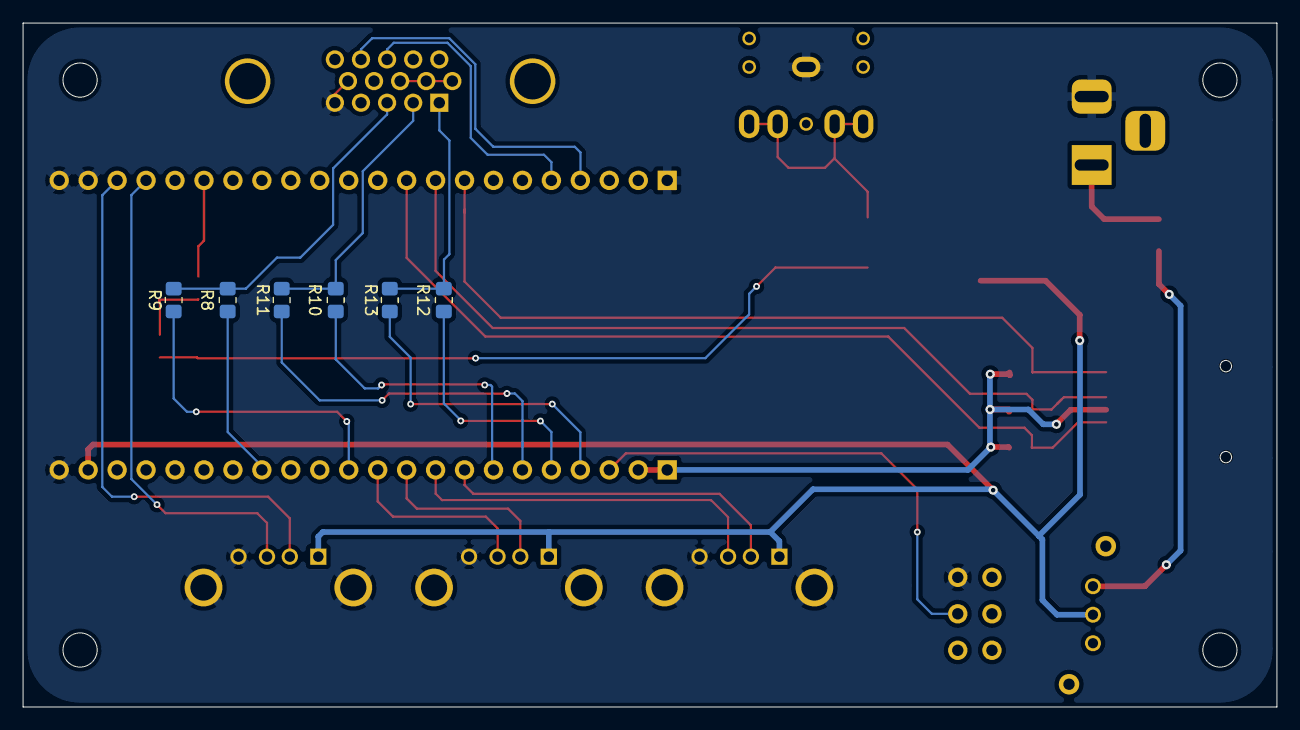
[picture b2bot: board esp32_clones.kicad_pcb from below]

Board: 2 copper layers, 110.0 x 60.0 mm, 26 parts (6 on the bottom side), 30 nets.

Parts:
C1: 220UF; CP_Elec_6.3x3
C2: 10UF; CP_Elec_5x4.5
C4: 100NF; C_0805_2012Metric_Pad1.18x1.45mm_HandSolder
C6: 47NF; C_0805_2012Metric_Pad1.18x1.45mm_HandSolder
F1: Fuse; Fuse_1210_3225Metric
J1: Barrel_Jack; BarrelJack_Horizontal
J2: Micro_SD_Card; Conn_uSDcard
J3: AudioJack2_Ground; PJ-307
J4: PS-12E05
J5: PS-22F05
J6, J7, J8: USB_A; TE_6364372-2
J9: DA15_Pins; DSUB-15-HD_Socket_Horizontal_P2.29x1.90mm_EdgePinOffset3.03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
R1, R4, R7: 10K; R_0805_2012Metric_Pad1.20x1.40mm_HandSolder
R2, R5: 330; R_0805_2012Metric_Pad1.20x1.40mm_HandSolder
R8, R10, R12: 1.2K; R_0805_2012Metric_Pad1.20x1.40mm_HandSolder
R9, R11, R13: 560; R_0805_2012Metric_Pad1.20x1.40mm_HandSolder
U1: ESP32-S3-WROOM-1

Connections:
+3.3V: J2.4 (VDD), R1.1, R4.1, R7.1, U1.23 (3V3), U1.24 (3V3)
+5V: C1.1, J4.2, J6.1 (VBUS), J7.1 (VBUS), J8.1 (VBUS), U1.43 (5V)
GND: C1.2, C4.2, C6.2, J1.2, J2.6 (VSS), J3.G, J5.3, J6.4 (GND), J6.5 (Shield), J7.4 (GND), J7.5 (Shield), J8.4 (GND), J8.5 (Shield), J9.5, J9.6, J9.7, J9.8, J9.10, U1.1 (GND), U1.2 (GND), U1.22 (GND), U1.44 (GND)
unnamed: C2.1, C4.1, R2.2
unnamed: C2.2, J3.S, J3.T
unnamed: C6.1, R2.1, R5.2
unnamed: F1.1, J1.1
unnamed: F1.2, J4.1
unnamed: J2.5 (CLK), R4.2, U1.14 (IO39)
unnamed: J2.3 (CMD), R7.2, U1.13 (IO38)
unnamed: J2.7 (DAT0), R1.2, U1.15 (IO40)
unnamed: J6.3 (D+), U1.33 (IO18)
unnamed: J6.2 (D-), U1.32 (IO17)
unnamed: J7.3 (D+), U1.31 (IO16)
unnamed: J7.2 (D-), U1.30 (IO15)
unnamed: J8.3 (D+), U1.4 (I020)
unnamed: J8.2 (D-), U1.3 (IO19)
unnamed: J9.13, U1.18 (IO02)
unnamed: J9.14, U1.19 (IO01)
unnamed: J9.1, R12.1, R13.2
unnamed: J9.2, R10.1, R11.2
unnamed: J9.3, R8.1, R9.2
unnamed: R13.1, U1.26 (IO04)
unnamed: R12.2, U1.27 (IO05)
unnamed: R11.1, U1.28 (IO06)
unnamed: R10.2, U1.29 (IO07)
unnamed: R9.1, U1.34 (IO08)
unnamed: R8.2, U1.37 (IO09)
unnamed: R5.1, U1.6 (IO47)
unnamed: J5.2, U1.25 (RST)

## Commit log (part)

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2026-06-25 Add font data and testing documentation
    - Added CoCO2_3_Fonts.txt containing font data for the emulator.
    - Created README file in the test directory to explain the purpose of the directory and provide information on PlatformIO Unit Testing.
    - Introduced ScrapBook.txt with various BASIC programs and notes related to disk transactions and graphics modes.
2026-06-30 Refactor code structure for improved readability and maintainability

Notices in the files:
hardware/esp32_clones/esp32_clones.kicad_pcb:
This work is licensed under a
